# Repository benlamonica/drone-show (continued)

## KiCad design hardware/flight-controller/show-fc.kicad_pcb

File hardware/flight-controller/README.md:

# Show FC: 2-layer flight controller for the drone show

A flight controller made for the show quad: RP2354B, two IMUs, a DPS368
barometer, microSD for logs and the show file, and ports for the RTK GPS
board, the light/Wi-Fi board, an RC receiver and the ESC. It is a redesign of
[OpenFC-Lite](https://github.com/OpenDrone-hw/OpenFC-Lite) rev3.3 (RP2354B,
6 layers, 0201 parts) for a **2-layer** board with **0603 parts** (0402 only
for decoupling right at the MCU and sensors) that PCBWay can build on its
standard service.

| Top | Bottom |
|---|---|
|  |  |

> **Status: fully routed.** KiCad 10 DRC (with schematic parity and zone
> refill) and ERC are clean: no errors, no warnings, nothing unconnected. The
> files in `fab/` are from this board. Go through
> [Check before the first order](#check-before-the-first-order) before
> ordering.

| | |
|---|---|
| MCU | RP2354B (QFN-80, 2 MB stacked flash, 48 GPIO), 12 MHz crystal |
| IMU | ICM-42688-P (IMU1, SPI0) and BMI270 (IMU2, SPI0, separate CS), same multi-source LGA-14 land |
| Barometer | DPS368 on I2C1, address 0x76 |
| Storage | microSD (SPI1), push-push Molex 104031-0811 |
| Input | 4S-6S through the ESC connector, 60 V-rated buck, 30 V TVS |
| Rails | 5 V / 3.5 A buck (LMR51635), 3.3 V LDO (LP5912-3.3), 1.8 V sensor LDO (LP5912-1.8), USB diode-OR |
| Ports | ESC (JST-SH 8), GPS (JST-GH 6, Pixhawk pinout), LIGHT (JST-GH 8), RC (JST-GH 4), SWD (JST-SH 3), USB-C |
| Board | 54 x 54 mm octagon, corners cut at 27 mm, 30.5 mm M3 stack, 2 layers, 1.6 mm, 1 oz, single-sided assembly |

## Why it looks like this

**2 layers.** The 6-layer original buries power and ground planes. Here both
outer layers carry signals, and each has a ground pour joined by stitching
vias. The 0.4 mm-pitch QFN escapes
on 0.2 mm tracks with 0.15 mm gaps, inside PCBWay's standard 6/6 mil.

**Bigger parts.** 0603 resistors and capacitors everywhere except the 22
decoupling capacitors and 7 resistors next to the MCU and sensors, which are
0402 so they can sit within a few millimetres of their pins.

**Size and shape.** The FC sits in the stack on the hub. The frame's arm
sockets start 27.7 mm from the centre along the arm axes, which is where the
FC's corners point (it is mounted rotated 45 degrees), so the corners are cut
at 27 mm. The flats are 54 mm apart: at 50 mm the MCU could not be routed on
two layers. The 30.5 mm hole pattern is from `frame/frame.py` (`STACK_SPACING`).

**Stacking.** All the show boards stack on the same 30.5 mm M3 pattern with
rubber standoffs between them: unplated 3.3 mm holes at ±15.25 mm, each with
a 7.5 mm copper-free circle (the project spec asks for at least 6.9 mm), and every part is on the top side, so the bottom is flat (the only things on
the bottom are the bare SWD debug pads).

**What changed from OpenFC-Lite.** The analog OSD chain, 10 V VTX rail and
VTX/camera connectors are gone (a show drone has no video). Added: a second
IMU from a different vendor, the DPS368, a TVS on the battery input, a 60 V
buck (6S plus ESC spikes), the LIGHT port with UART flow control, a reset
button and an SWD port for bringing up the ArduPilot port.

## Ports

Pin 1 is marked on the silkscreen. "Out" is from the FC.

| Port | Pins |
|---|---|
| J3 ESC (SH 8, OpenFC/Betaflight standard) | 1 VBAT, 2 GND, 3 current sense in, 4 ESC telemetry in, 5 M1, 6 M2, 7 M3, 8 M4 |
| J4 GPS (GH 6, Pixhawk GPS1) | 1 +5V, 2 TX out, 3 RX in, 4 SCL, 5 SDA, 6 GND. I2C0 for the RTK board's compass. PPS goes to pad TP9 |
| J5 LIGHT (GH 8) | 1 +5V, 2 TX out, 3 RX in, 4 CTS in, 5 RTS out, 6 LED data out (47 R), 7 GPIO, 8 GND |
| J6 RC (GH 4) | 1 +5V, 2 TX out, 3 RX in, 4 GND (CRSF/SBUS, PIO UART) |
| J8 SWD (SH 3, Raspberry Pi debug pinout) | 1 SWCLK, 2 GND, 3 SWDIO |
| SWD debug pads (bottom, TP14-TP18) | 1 mm round pads at 2.54 mm pitch along the right edge behind J8, labelled on the bottom silkscreen. Top to bottom (J8 end first): SWDIO, GND, SWCLK, 3V3, RUN |
| J1 USB-C | Device, full speed. Powers the logic (not the 5 V ports) through D5 |

Pads: TP1 VBAT, TP2/TP4/TP11 GND, TP3 +5V, TP10 +3V3, TP5/TP6 buzzer (+5V and
low side), TP7/TP8 AUX5/AUX6 (PWM), TP9 GPS PPS in, TP12/TP13 TELEM2 TX/RX.

Debug pads (bottom side, for a pogo-pin jig or a clip when the JST cable is
not handy): TP14 SWDIO, TP15 GND, TP16 SWCLK, TP17 3V3, TP18 RUN. 3V3 is the
board's own rail: power the board from USB or the battery, and do not feed
3.3 V in from the debugger. RUN is the RP2354B reset (low = reset), the same
net as SW2.

## GPIO map

| GPIO | Function | GPIO | Function |
|---|---|---|---|
| 0, 1 | TELEM2 TX/RX (pads, PIO UART) | 24, 25 | Status LEDs blue, green |
| 2, 3 | RC TX/RX (PIO UART) | 26 | Buzzer FET |
| 4, 5 | I2C0 SDA/SCL (GPS compass) | 27 | Free |
| 6, 7 | I2C1 SDA/SCL (DPS368) | 28-31 | M1-M4 (DShot, PIO) |
| 8-11 | SPI1 MISO, CS, SCK, MOSI (microSD) | 32-35 | UART0 TX, RX, CTS, RTS (LIGHT) |
| 12, 13 | IMU2 CS, INT | 36 | LIGHT GPIO |
| 14, 15 | IMU1 INT, CLKIN (32 kHz PWM) | 37 | Free (microSD card detect not connected) |
| 16-19 | SPI0 MISO, CS1, SCK, MOSI (IMUs) | 38, 39 | AUX5, AUX6 |
| 20, 21 | UART1 TX/RX (GPS) | 40 (ADC0) | VBAT, 100k/10k divider (scale 11.0) |
| 22 | GPS PPS | 41 (ADC1) | ESC current, 1k/100n filter |
| 23 | ESC telemetry RX (PIO UART) | 42 | LED data to LIGHT; 43-47 free |

QSPI_SS is the BOOTSEL button (SW1). SW2 is reset (RUN).

## Files

| Path | What |
|---|---|
| `show-fc.kicad_pro`, `.kicad_sch`, `.kicad_pcb` | The KiCad project, saved in KiCad 10 format (KiCad 9 and older cannot open it) |
| `show-fc.kicad_dru` | PCBWay rules by name, plus board rules |
| `showfc.kicad_sym`, `showfc.pretty/` | Project symbols and the three footprints KiCad's library lacks |
| `tools/design.py` | **The circuit**: every part, footprint, order code and net |
| `tools/make_schematic.py` | Writes the schematic and symbol library from `design.py` |
| `tools/make_footprints.py` | Writes `showfc.pretty` |
| `tools/make_board.py` | Outline, rules, footprints, nets and placement |
| `tools/route.py` | Freerouting, ground pours, stitching vias, DRC report |
| `tools/finish.py` | A second Freerouting pass that keeps the existing wiring |
| `tools/handroute.py`, `finish_loop.sh` | A small grid router for leftover connections (experimental) |
| `tools/make_fab.py` | Gerbers, drill, pick-and-place and the PCBWay BOM into `fab/` |
| `fab/` | What you upload to PCBWay |

The schematic is generated: to change the circuit, edit `design.py` and
re-run `make_schematic.py`. The board is not: `show-fc.kicad_pcb` was routed
by Freerouting and then finished by hand in KiCad 10 (the last four tracks,
the SWD pads, R16 and R17 swapped so the divider's VBAT pad sits next to C24),
so it is the master copy. Edit it in KiCad; re-running `make_board.py` or
`route.py` starts again from an unrouted board and throws that work away. Two
of the hand-finished tracks are long because the middle of the board is full:
BUZZER and RUN (to the SWD pads) run around the mounting holes on the bottom
layer. Both are slow signals, so the length does not matter.

The original from-scratch pipeline, for reference:

```sh
cd hardware/flight-controller/tools
python3 make_footprints.py
python3 make_schematic.py
python3 route.py --passes 50   # runs make_board.py, then routes (about 40 min)
python3 finish.py              # optional second pass on the result
python3 make_fab.py
```

The scripts need KiCad's Python (`pcbnew`) and `kicad-cli`, Java 17+ and
[Freerouting 1.9](https://github.com/freerouting/freerouting/releases/tag/v1.9.0)
(`FREEROUTING_JAR`).

## Ordering at PCBWay

PCB: 2 layers, 54 x 54 mm, FR-4 TG150, 1.6 mm, 1 oz, min track/spacing
6/6 mil, min hole 0.3 mm, green mask, white silk, HASL lead-free or ENIG
(ENIG is flatter for the QFN and LGA parts). Assembly: top side only, upload
`fab/show-fc-revA-bom.csv` and `fab/show-fc-revA-cpl.csv`.

## Check before the first order

These are the things I could not verify from here:

1. **DPS368 pin order.** The footprint follows the PG-VLGA-8-2 package
   (pins 1-4 along one long edge, 5-8 back along the other, counter-clockwise
   from the top). A mirrored land would swap VDD and GND, so compare
   `showfc.pretty/Infineon_VLGA-8_2.0x2.5mm_P0.65mm` with the current DPS368
   datasheet. The DPS310 is pin-compatible but marked not recommended for new
   designs, so the BOM uses the DPS368.
2. **ERC and DRC.** Both pass in KiCad 10.0.5
   (`kicad-cli sch erc show-fc.kicad_sch` and
   `kicad-cli pcb drc --schematic-parity --refill-zones show-fc.kicad_pcb`).
   Re-run them after any edit.
3. **Connector direction.** The JST and USB-C footprints face out of the
   board edges; check the plug side against the frame before ordering.
4. **The core-regulator inductor (L1).** The RP2350 datasheet asks for the
   Abracon AOTA-B201610S3R3-101-T with its dot on VREG_LX. The footprint is
   the standard 2016 land.
5. **Order codes.** MPNs are filled in; LCSC numbers only where OpenFC-Lite
   already used the part. PCBWay sources by MPN.

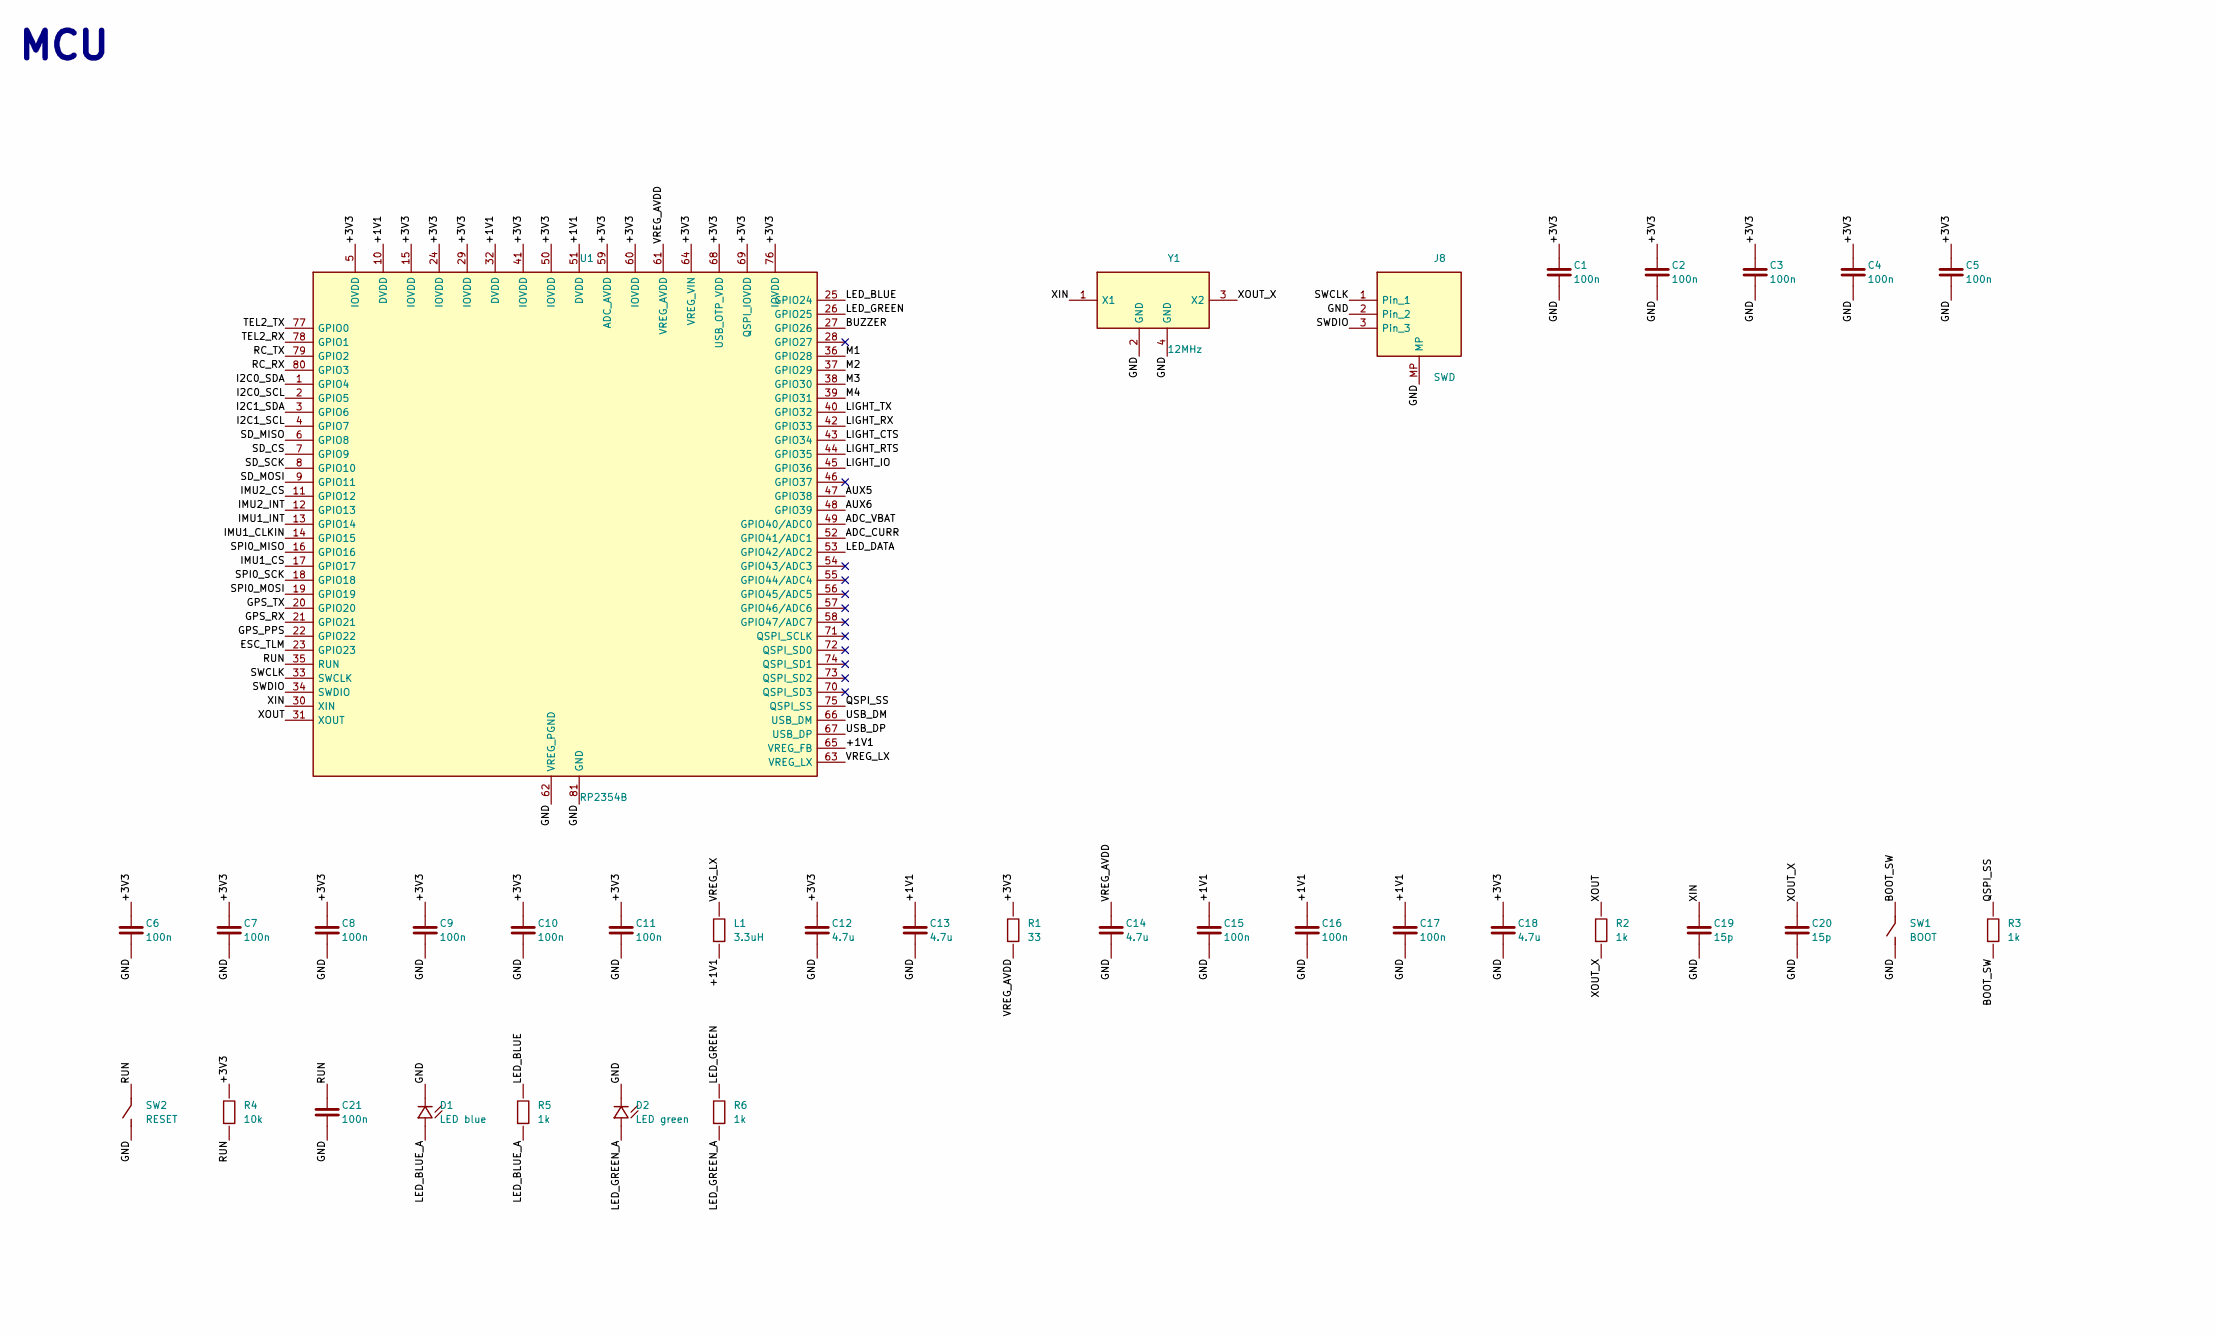
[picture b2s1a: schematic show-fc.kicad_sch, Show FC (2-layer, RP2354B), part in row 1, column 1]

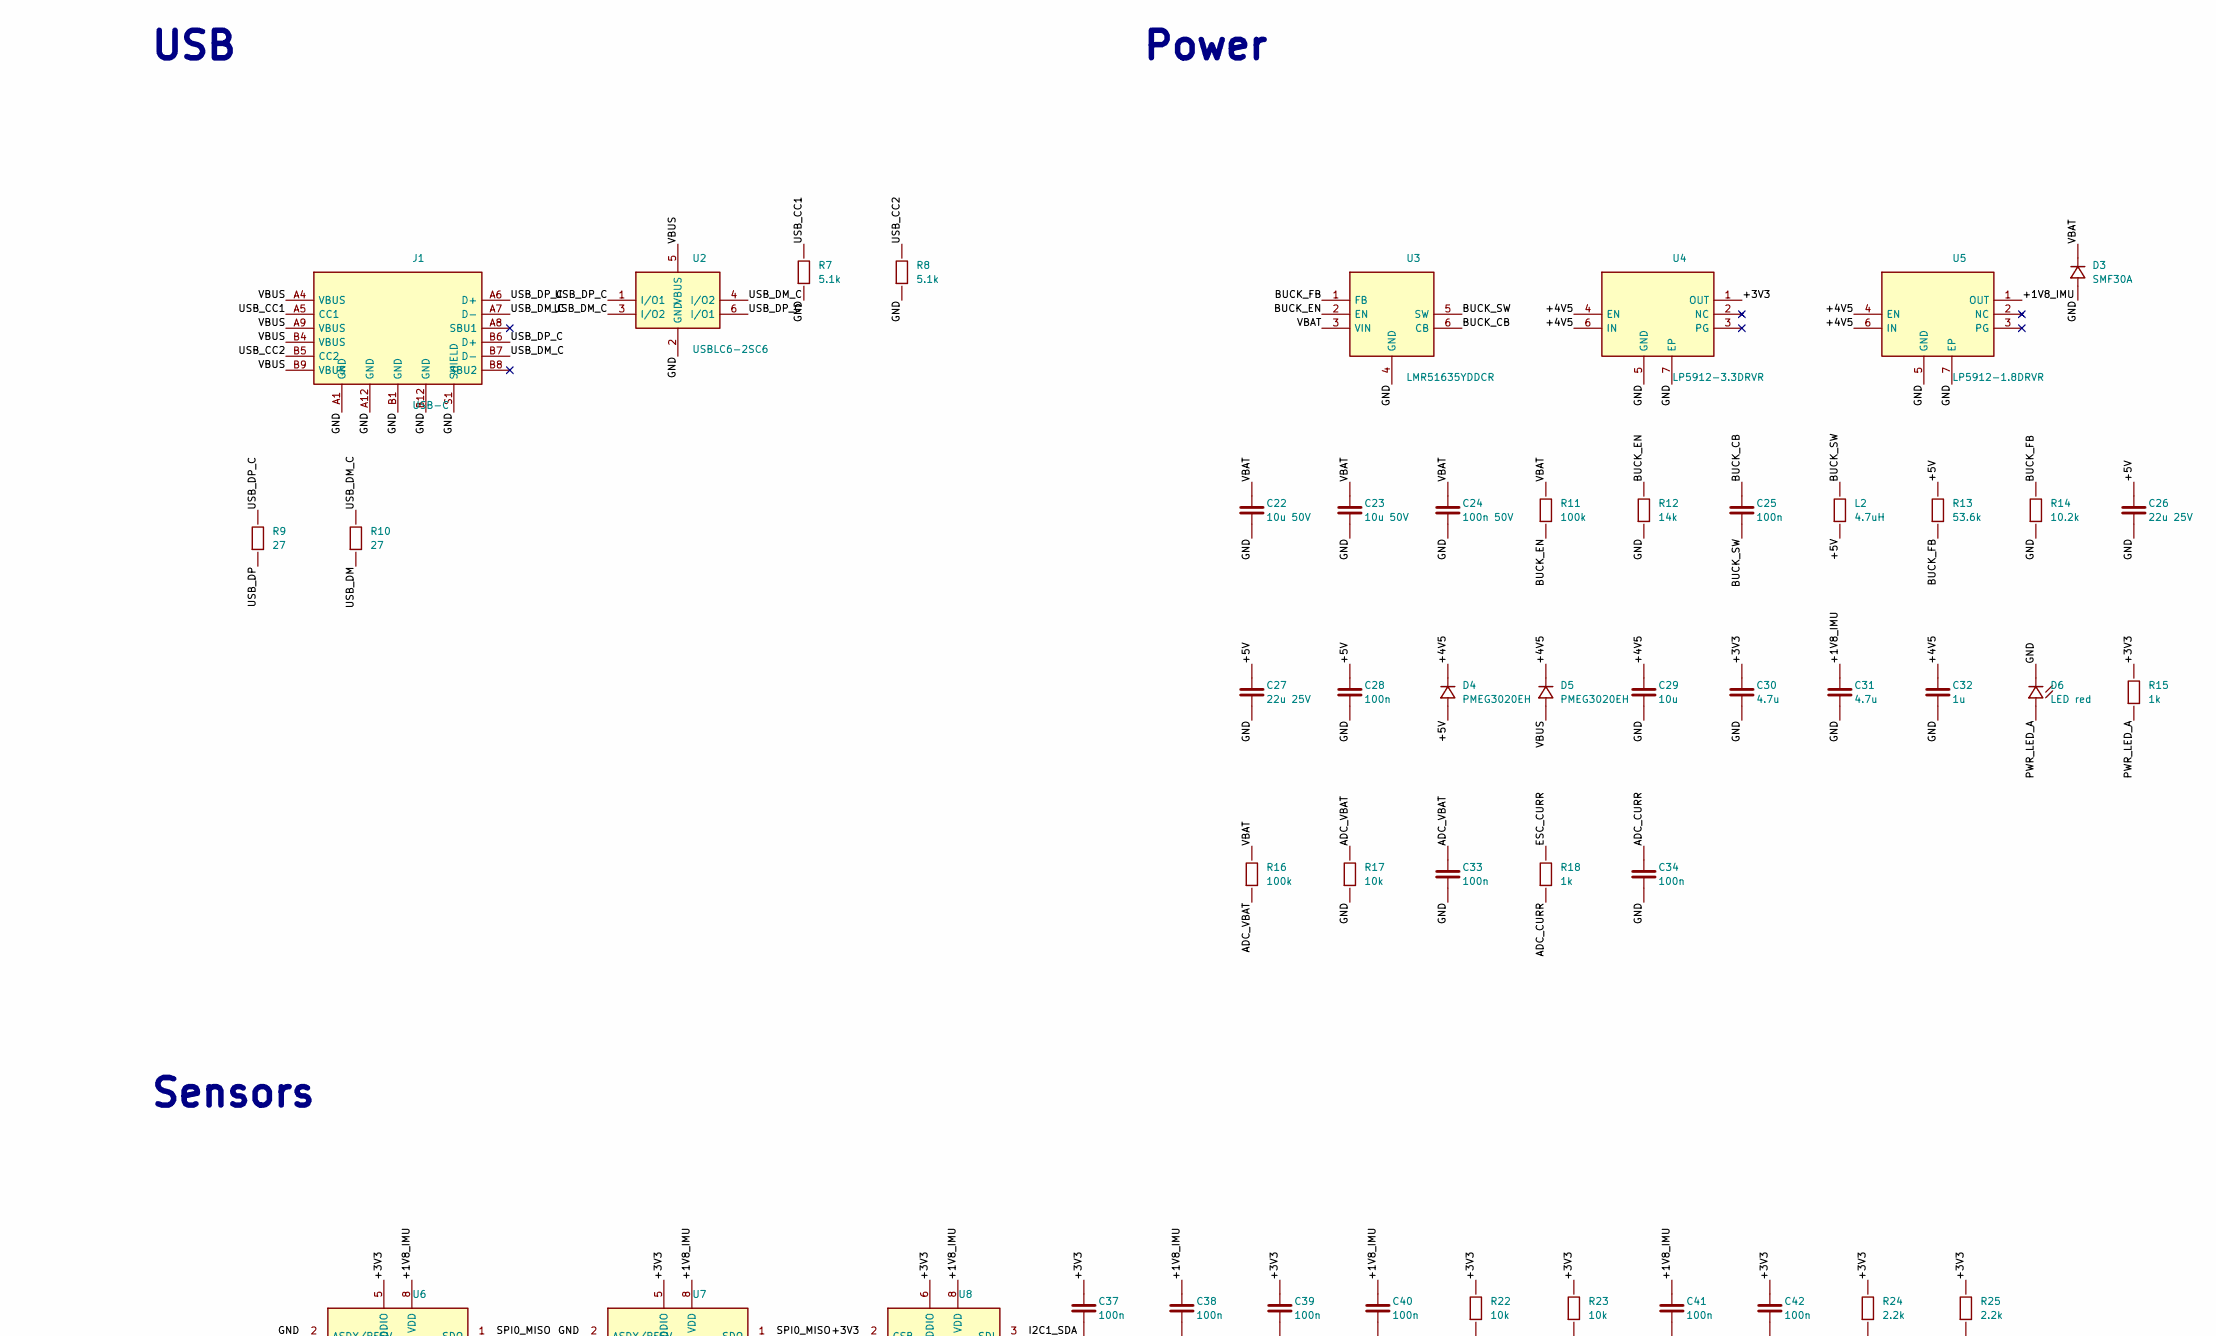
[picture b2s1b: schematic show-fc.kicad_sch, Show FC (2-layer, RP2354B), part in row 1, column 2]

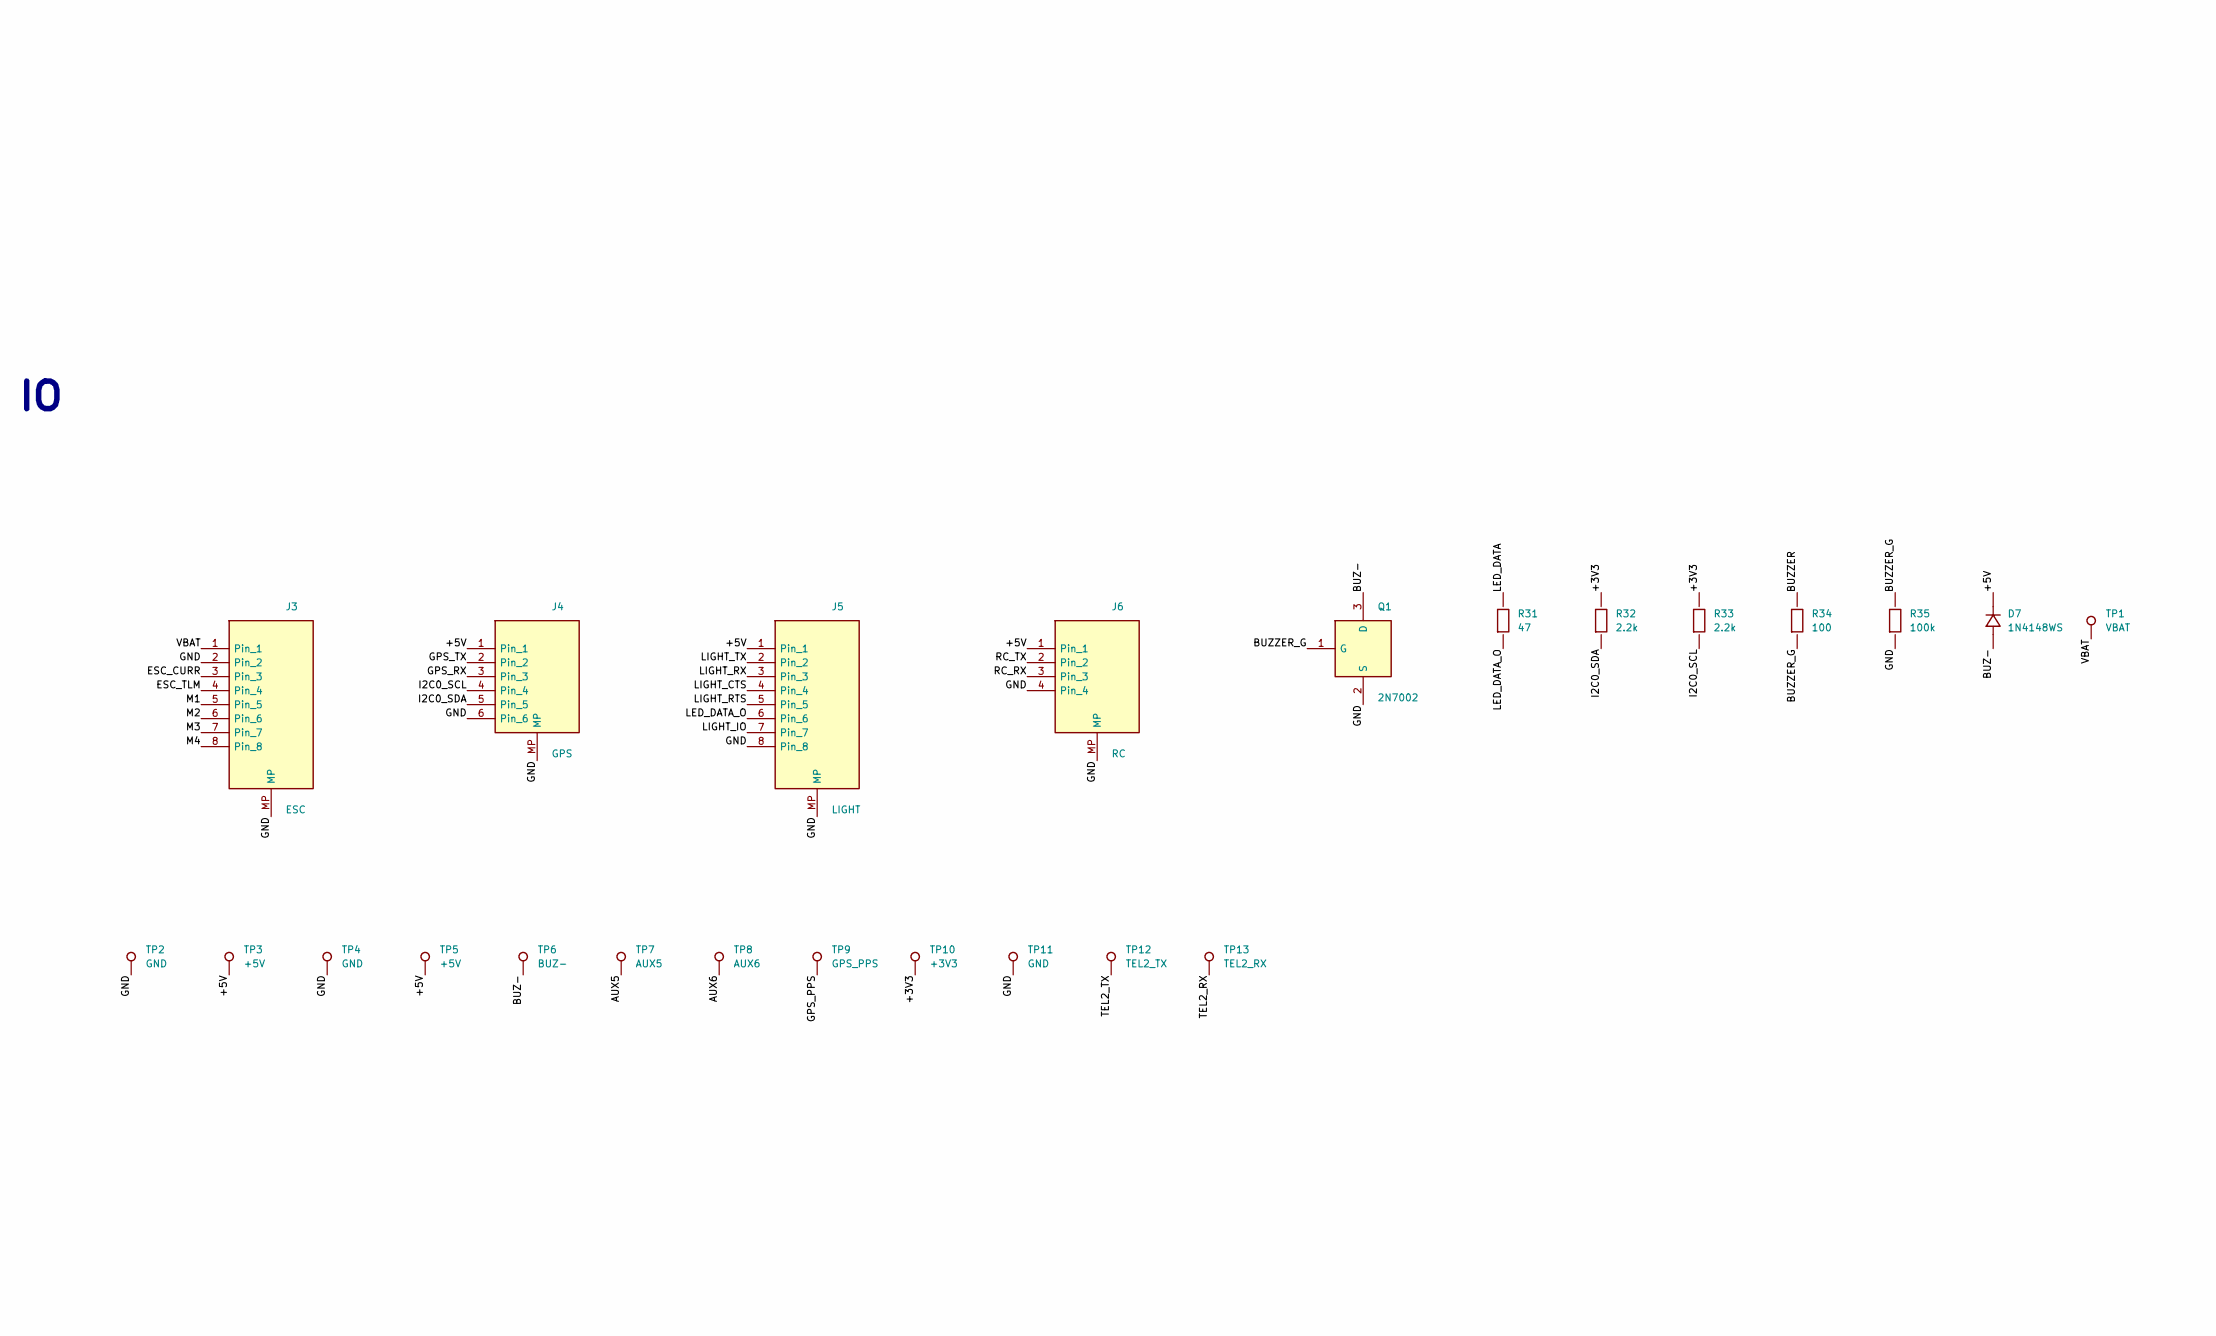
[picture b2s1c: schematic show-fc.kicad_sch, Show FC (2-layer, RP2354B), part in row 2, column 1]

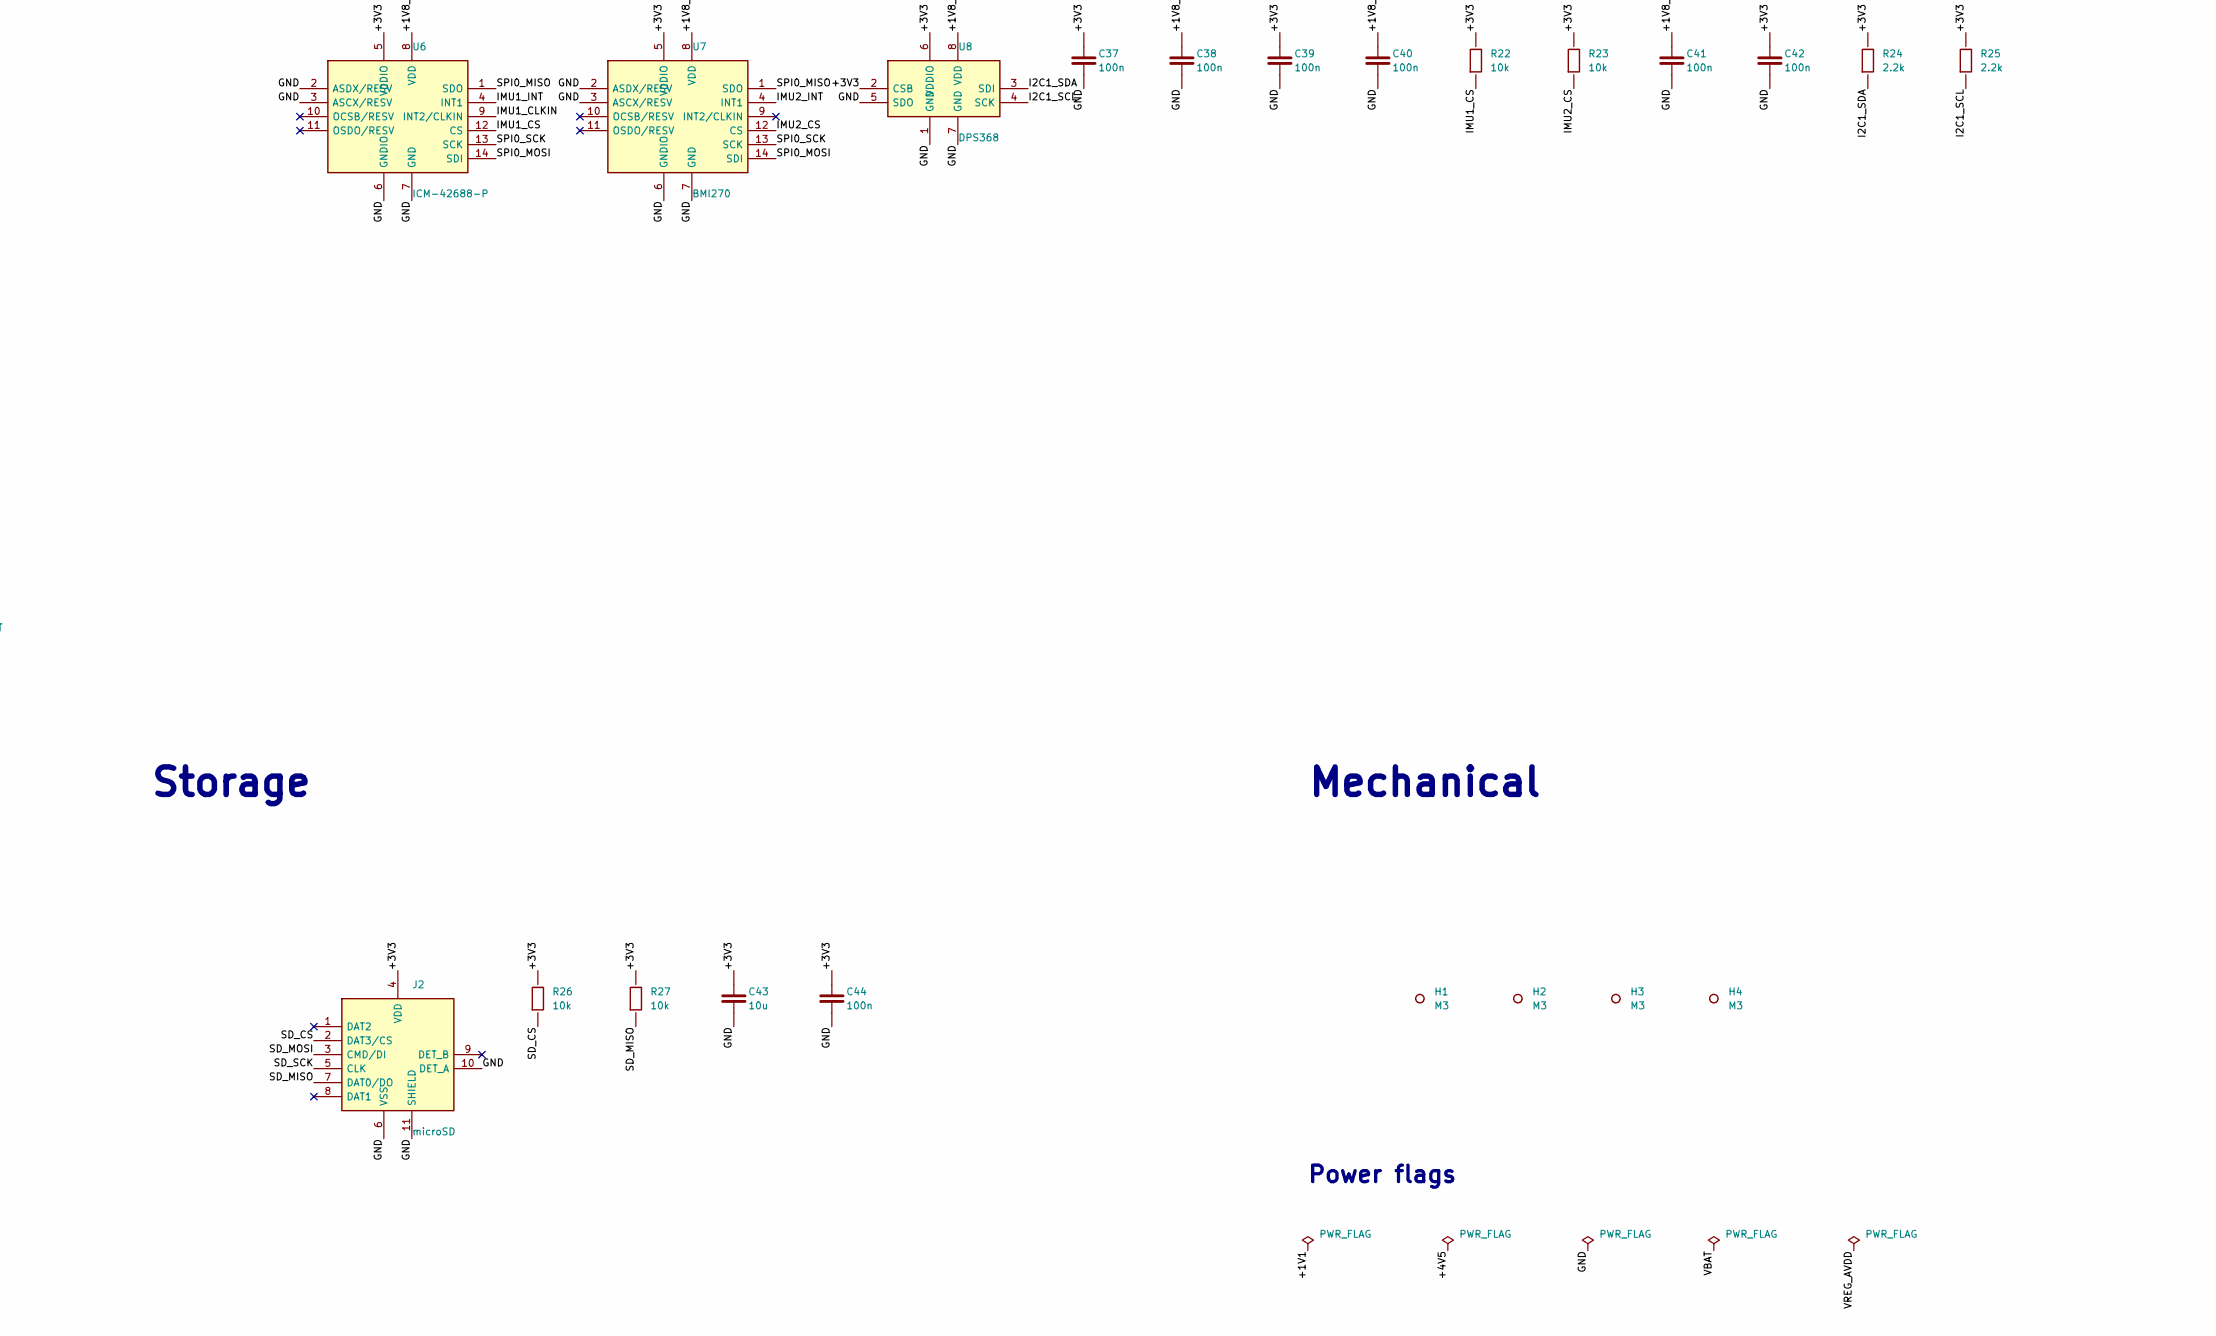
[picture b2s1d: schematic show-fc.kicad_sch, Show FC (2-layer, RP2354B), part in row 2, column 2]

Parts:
C1, C2, C3, C4, C5, C6, C7, C8, C9, C10, C11, C15, C16, C17, C37, C38, C39, C40, C41, C42: 100n; C_0402_1005Metric; MPN GRM155R71C104KA88D
C12, C13, C14, C18, C30, C31: 4.7u; C_0603_1608Metric; MPN GRM188R61A475KE15D
C19, C20: 15p; C_0402_1005Metric; MPN GRM1555C1H150JA01D
C21, C25, C28, C33, C34, C44: 100n; C_0603_1608Metric; MPN GCM188R71H104KA57D
C22, C23: 10u 50V; C_1206_3216Metric; MPN GRM31CR61H106KA12L
C24: 100n 50V; C_0603_1608Metric; MPN GCM188R71H104KA57D
C26, C27: 22u 25V; C_1206_3216Metric; MPN GRM31CR61E226KE15L
C29, C43: 10u; C_0805_2012Metric; MPN GRM21BR61C106KE15L
C32: 1u; C_0603_1608Metric; MPN GRM188R61E105KA12D
D1: LED blue; LED_0603_1608Metric; MPN 150060BS75000
D2: LED green; LED_0603_1608Metric; MPN 150060VS75000
D3: SMF30A; D_SOD-123F; MPN SMF30A
D4, D5: PMEG3020EH; D_SOD-123F; MPN PMEG3020EH,115
D6: LED red; LED_0603_1608Metric; MPN 150060RS75000
D7: 1N4148WS; D_SOD-323; MPN 1N4148WS
H1, H2, H3, H4: M3; MountingHole_3.3mm_M3_Stack
J1: USB-C; USB_C_Receptacle_GCT_USB4105-xx-A_16P_TopMnt_Horizontal; MPN USB4105-GF-A
J2: microSD; microSD_HC_Molex_104031-0811; MPN 1040310811
J3: ESC; JST_SH_SM08B-SRSS-TB_1x08-1MP_P1.00mm_Horizontal; MPN SM08B-SRSS-TB(LF)(SN); LCSC C160407
J4: GPS; JST_GH_SM06B-GHS-TB_1x06-1MP_P1.25mm_Horizontal; MPN SM06B-GHS-TB(LF)(SN)
J5: LIGHT; JST_GH_SM08B-GHS-TB_1x08-1MP_P1.25mm_Horizontal; MPN SM08B-GHS-TB(LF)(SN)
J6: RC; JST_GH_SM04B-GHS-TB_1x04-1MP_P1.25mm_Horizontal; MPN SM04B-GHS-TB(LF)(SN)
J8: SWD; JST_SH_SM03B-SRSS-TB_1x03-1MP_P1.00mm_Horizontal; MPN SM03B-SRSS-TB(LF)(SN)
L1: 3.3uH; L_Murata_DFE201610P; MPN AOTA-B201610S3R3-101-T
L2: 4.7uH; L_Wuerth_MAPI-4020; MPN 74438357047
Q1: 2N7002; SOT-23; MPN 2N7002LT1G
R1: 33; R_0603_1608Metric; MPN RC0603FR-0733L
R2: 1k; R_0402_1005Metric; MPN RC0402FR-071KL
R3, R5, R6, R15, R18: 1k; R_0603_1608Metric; MPN RC0603FR-071KL
R4, R17, R26, R27: 10k; R_0603_1608Metric; MPN RC0603FR-0710KL
R7, R8: 5.1k; R_0603_1608Metric; MPN RC0603FR-075R1KL
R9, R10: 27; R_0402_1005Metric; MPN RC0402FR-0727L
R11, R16, R35: 100k; R_0603_1608Metric; MPN RC0603FR-07100KL
R12: 14k; R_0603_1608Metric; MPN RC0603FR-0714KL
R13: 53.6k; R_0603_1608Metric; MPN RC0603FR-0753R6KL
R14: 10.2k; R_0603_1608Metric; MPN RC0603FR-0710R2KL
R22, R23: 10k; R_0402_1005Metric; MPN RC0402FR-0710KL
R24, R25: 2.2k; R_0402_1005Metric; MPN RC0402FR-072R2KL
R31: 47; R_0603_1608Metric; MPN RC0603FR-0747L
R32, R33: 2.2k; R_0603_1608Metric; MPN RC0603FR-072R2KL
R34: 100; R_0603_1608Metric; MPN RC0603FR-07100L
SW1: BOOT; SW_SPST_B3U-1000P; MPN B3U-1000P
SW2: RESET; SW_SPST_B3U-1000P; MPN B3U-1000P
TP1: VBAT; TestPoint_Pad_D1.5mm
TP2, TP4, TP11: GND; TestPoint_Pad_D1.5mm
TP3, TP5: +5V; TestPoint_Pad_D1.5mm
TP6: BUZ-; TestPoint_Pad_D1.5mm
TP7: AUX5; TestPoint_Pad_D1.5mm
TP8: AUX6; TestPoint_Pad_D1.5mm
TP9: GPS_PPS; TestPoint_Pad_D1.5mm
TP10: +3V3; TestPoint_Pad_D1.5mm
TP12: TEL2_TX; TestPoint_Pad_D1.5mm
TP13: TEL2_RX; TestPoint_Pad_D1.5mm
U1: RP2354B; QFN-80-1EP_10x10mm_P0.4mm_EP3.4x3.4mm; MPN RP2354B; LCSC C39843328
U2: USBLC6-2SC6; SOT-23-6; MPN USBLC6-2SC6
U3: LMR51635YDDCR; SOT-23-6; MPN LMR51635YDDCR; LCSC C45262770
U4: LP5912-3.3DRVR; WSON-6-1EP_2x2mm_P0.65mm_EP1x1.6mm_ThermalVias; MPN LP5912-3.3DRVR; LCSC C524780
U5: LP5912-1.8DRVR; WSON-6-1EP_2x2mm_P0.65mm_EP1x1.6mm_ThermalVias; MPN LP5912-1.8DRVR; LCSC C2876234
U6: ICM-42688-P; LGA-14_3x2.5mm_P0.5mm; MPN ICM-42688-P
U7: BMI270; LGA-14_3x2.5mm_P0.5mm; MPN BMI270; LCSC C2836813
U8: DPS368; Infineon_VLGA-8_2.0x2.5mm_P0.65mm; MPN DPS368XTSA1
Y1: 12MHz; Crystal_SMD_3225-4Pin_3.2x2.5mm; MPN ABM8-272-T3; LCSC C20625731

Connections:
+1V1: C13.1, C15.1, C16.1, C17.1, L1.2, U1.10 (DVDD), U1.32 (DVDD), U1.51 (DVDD), U1.65 (VREG_FB)
+1V8_IMU: C31.1, C38.1, C40.1, C41.1, U5.1 (OUT), U6.8 (VDD), U7.8 (VDD), U8.8 (VDD)
+3V3: C1.1, C2.1, C3.1, C4.1, C5.1, C6.1, C7.1, C8.1, C9.1, C10.1, C11.1, C12.1, C18.1, C30.1, C37.1, C39.1, C42.1, C43.1, C44.1, J2.4 (VDD), R1.1, R4.1, R15.1, R22.1, R23.1, R24.1, R25.1, R26.1, R27.1, R32.1, R33.1, TP10.1, U1.5 (IOVDD), U1.15 (IOVDD), U1.24 (IOVDD), U1.29 (IOVDD), U1.41 (IOVDD), U1.50 (IOVDD), U1.59 (ADC_AVDD), U1.60 (IOVDD), U1.64 (VREG_VIN), U1.68 (USB_OTP_VDD), U1.69 (QSPI_IOVDD), U1.76 (IOVDD), U4.1 (OUT), U6.5 (VDDIO), U7.5 (VDDIO), U8.2 (CSB), U8.6 (VDDIO); also elsewhere on the board
+4V5: C29.1, C32.1, D4.1 (K), D5.1 (K), U4.4 (EN), U4.6 (IN), U5.4 (EN), U5.6 (IN)
+5V: C26.1, C27.1, C28.1, D4.2 (A), D7.1 (K), J4.1, J5.1, J6.1, L2.2, R13.1, TP3.1, TP5.1
ADC_CURR: C34.1, R18.2, U1.52 (GPIO41/ADC1)
ADC_VBAT: C33.1, R16.2, R17.1, U1.49 (GPIO40/ADC0)
AUX5: TP7.1, U1.47 (GPIO38)
AUX6: TP8.1, U1.48 (GPIO39)
BOOT_SW: R3.2, SW1.1
BUCK_CB: C25.1, U3.6 (CB)
BUCK_EN: R11.2, R12.1, U3.2 (EN)
BUCK_FB: R13.2, R14.1, U3.1 (FB)
BUCK_SW: C25.2, L2.1, U3.5 (SW)
BUZ-: D7.2 (A), Q1.3 (D), TP6.1
BUZZER: R34.1, U1.27 (GPIO26)
BUZZER_G: Q1.1 (G), R34.2, R35.1
ESC_CURR: J3.3, R18.1
ESC_TLM: J3.4, U1.23 (GPIO23)
GND: C1.2, C2.2, C3.2, C4.2, C5.2, C6.2, C7.2, C8.2, C9.2, C10.2, C11.2, C12.2, C13.2, C14.2, C15.2, C16.2, C17.2, C18.2, C19.2, C20.2, C21.2, C22.2, C23.2, C24.2, C26.2, C27.2, C28.2, C29.2, C30.2, C31.2, C32.2, C33.2, C34.2, C37.2, C38.2, C39.2, C40.2, C41.2, C42.2, C43.2, C44.2, D1.1 (K), D2.1 (K), D3.2 (A), D6.1 (K), J1.A1 (GND), J1.A12 (GND), J1.B1 (GND), J1.B12 (GND), J1.S1 (SHIELD), J2.6 (VSS), J2.10 (DET_A), J2.11 (SHIELD), J3.2, J3.MP, J4.6, J4.MP, J5.8, J5.MP, J6.4, J6.MP, J8.2, J8.MP, Q1.2 (S), R7.2, R8.2, R12.2, R14.2, R17.2, R35.2, SW1.2, SW2.2, TP2.1, TP4.1, TP11.1, U1.62 (VREG_PGND), U1.81 (GND), U2.2 (GND), U3.4 (GND), U4.5 (GND), U4.7 (EP), U5.5 (GND), U5.7 (EP), U6.2 (ASDX/RESV), U6.3 (ASCX/RESV), U6.6 (GNDIO), U6.7 (GND), U7.2 (ASDX/RESV), U7.3 (ASCX/RESV), U7.6 (GNDIO), U7.7 (GND), U8.1 (GND), U8.5 (SDO), U8.7 (GND), Y1.2 (GND), Y1.4 (GND); also elsewhere on the board
GPS_PPS: TP9.1, U1.22 (GPIO22)
GPS_RX: J4.3, U1.21 (GPIO21)
GPS_TX: J4.2, U1.20 (GPIO20)
I2C0_SCL: J4.4, R33.2, U1.2 (GPIO5)
I2C0_SDA: J4.5, R32.2, U1.1 (GPIO4)
I2C1_SCL: R25.2, U1.4 (GPIO7), U8.4 (SCK)
I2C1_SDA: R24.2, U1.3 (GPIO6), U8.3 (SDI)
IMU1_CLKIN: U1.14 (GPIO15), U6.9 (INT2/CLKIN)
IMU1_CS: R22.2, U1.17 (GPIO17), U6.12 (CS)
IMU1_INT: U1.13 (GPIO14), U6.4 (INT1)
IMU2_CS: R23.2, U1.11 (GPIO12), U7.12 (CS)
IMU2_INT: U1.12 (GPIO13), U7.4 (INT1)
LED_BLUE: R5.1, U1.25 (GPIO24)
LED_BLUE_A: D1.2 (A), R5.2
LED_DATA: R31.1, U1.53 (GPIO42/ADC2)
LED_DATA_O: J5.6, R31.2
LED_GREEN: R6.1, U1.26 (GPIO25)
LED_GREEN_A: D2.2 (A), R6.2
LIGHT_CTS: J5.4, U1.43 (GPIO34)
LIGHT_IO: J5.7, U1.45 (GPIO36)
LIGHT_RTS: J5.5, U1.44 (GPIO35)
LIGHT_RX: J5.3, U1.42 (GPIO33)
LIGHT_TX: J5.2, U1.40 (GPIO32)
M1: J3.5, U1.36 (GPIO28)
M2: J3.6, U1.37 (GPIO29)
M3: J3.7, U1.38 (GPIO30)
M4: J3.8, U1.39 (GPIO31)
PWR_LED_A: D6.2 (A), R15.2
QSPI_SS: R3.1, U1.75 (QSPI_SS)
RC_RX: J6.3, U1.80 (GPIO3)
RC_TX: J6.2, U1.79 (GPIO2)
RUN: C21.1, R4.2, SW2.1, U1.35 (RUN); also elsewhere on the board
SD_CS: J2.2 (DAT3/CS), R26.2, U1.7 (GPIO9)
SD_MISO: J2.7 (DAT0/DO), R27.2, U1.6 (GPIO8)
SD_MOSI: J2.3 (CMD/DI), U1.9 (GPIO11)
SD_SCK: J2.5 (CLK), U1.8 (GPIO10)
SPI0_MISO: U1.16 (GPIO16), U6.1 (SDO), U7.1 (SDO)
SPI0_MOSI: U1.19 (GPIO19), U6.14 (SDI), U7.14 (SDI)
SPI0_SCK: U1.18 (GPIO18), U6.13 (SCK), U7.13 (SCK)
SWCLK: J8.1, U1.33 (SWCLK); also elsewhere on the board
SWDIO: J8.3, U1.34 (SWDIO); also elsewhere on the board
TEL2_RX: TP13.1, U1.78 (GPIO1)
TEL2_TX: TP12.1, U1.77 (GPIO0)
USB_CC1: J1.A5 (CC1), R7.1
USB_CC2: J1.B5 (CC2), R8.1
USB_DM: R10.2, U1.66 (USB_DM)
USB_DM_C: J1.A7 (D-), J1.B7 (D-), R10.1, U2.3 (I/O2), U2.4 (I/O2)
USB_DP: R9.2, U1.67 (USB_DP)
USB_DP_C: J1.A6 (D+), J1.B6 (D+), R9.1, U2.1 (I/O1), U2.6 (I/O1)
VBAT: C22.1, C23.1, C24.1, D3.1 (K), J3.1, R11.1, R16.1, TP1.1, U3.3 (VIN)
VBUS: D5.2 (A), J1.A4 (VBUS), J1.A9 (VBUS), J1.B4 (VBUS), J1.B9 (VBUS), U2.5 (VBUS)
VREG_AVDD: C14.1, R1.2, U1.61 (VREG_AVDD)
VREG_LX: L1.1, U1.63 (VREG_LX)
XIN: C19.1, U1.30 (XIN), Y1.1 (X1)
XOUT: R2.1, U1.31 (XOUT)
XOUT_X: C20.1, R2.2, Y1.3 (X2)

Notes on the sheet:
MCU
USB
Power
Sensors
Storage
Mechanical
Power flags
